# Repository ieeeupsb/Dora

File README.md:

View this project on [CADLAB.io](https://cadlab.io/project/1889). 

# Rasbot

## What is it?
This is a small differential terrestrial robot with all the sensors one can fit.
Its purpose is to have all the sensors and interfaces one can imagine so it can be used for research in various topics as well as different competitions.

Since its goal is to be resourceful in terms of sensing and actuating capabilities the design has expandability in mind. Therefore, there are a lot of exposed pins for modular expansions to the robot.

### Getting Support
There is extensive documentation on the Wiki page here on GitHub that covers the robot's design (hardware and software) as well as how to use this robot.

If you are a user of this robot and something is not working on your side please help us improve it. Open an issue here on GitHub!

### Contributing
Be it hardware or software, you can freely contribute to this project. Usually the Issues page here on GitHub has work that needs to be done. You are free to solve one yourself. Even if you are not familiar with hardware or software you can simply create new issues suggesting new things or changes/fixes to the current design.

This project is configured with CADLAB.io so visual differences of changes can be analysed.

If you are a contributor to this project keep in mind that pushing to the master branch is protected and can be only done by first creating a branch and then file a Pull Request which has to have at least two reviewers before it can be merged. This is meant to improve the quality of the project.

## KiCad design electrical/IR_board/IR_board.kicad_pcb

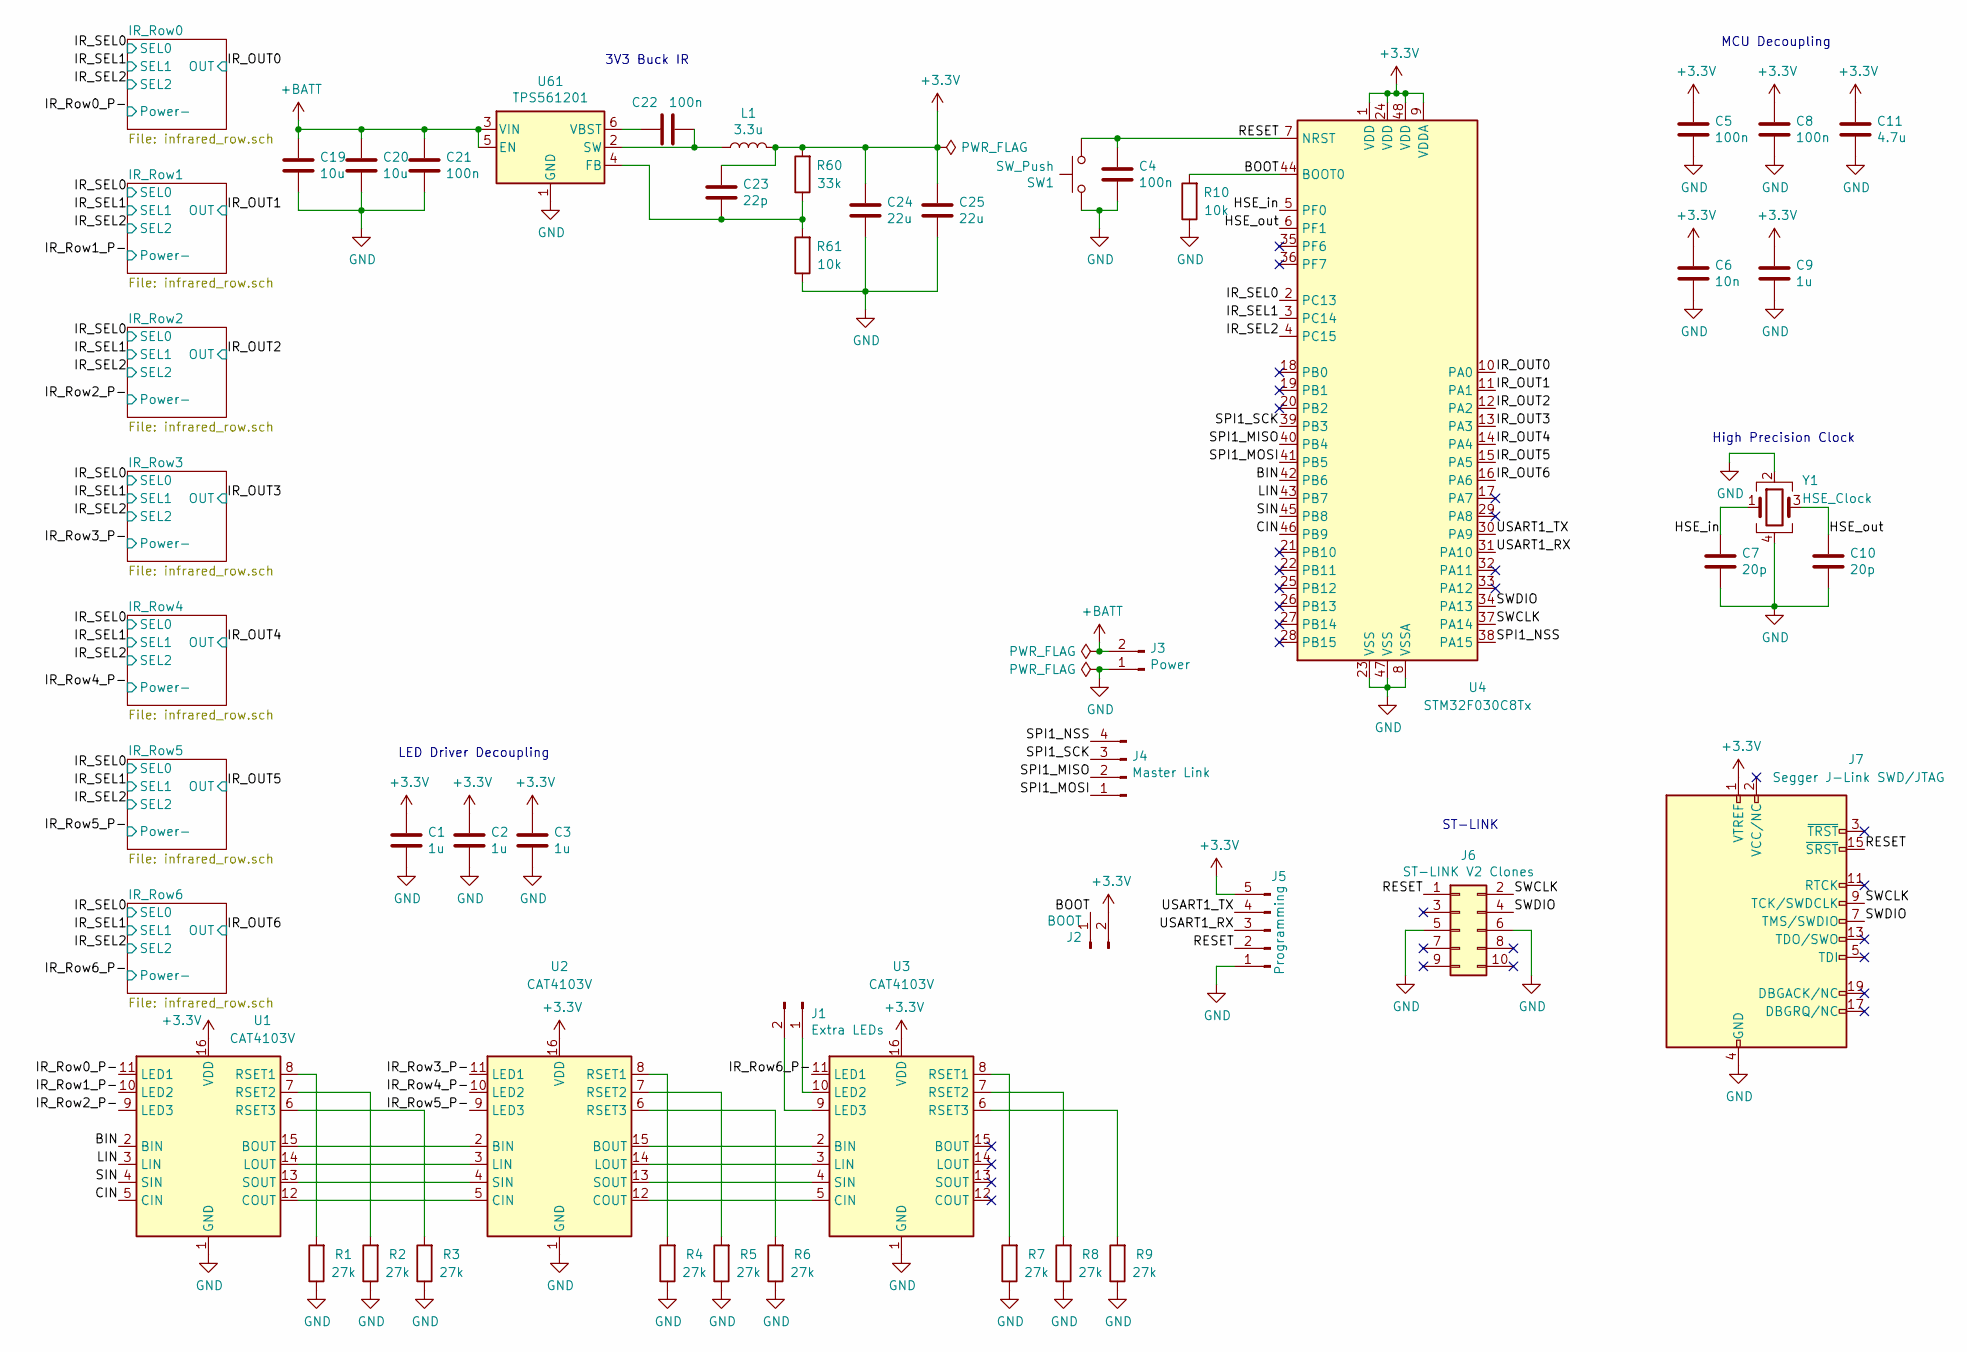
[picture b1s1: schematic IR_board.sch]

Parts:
C1, C2, C3, C9: 1u; C_0603_1608Metric
C4, C5, C8: 100n; C_0603_1608Metric
C6: 10n; C_0603_1608Metric
C7, C10: 20p; C_0603_1608Metric
C11: 4.7u; C_0603_1608Metric
C19, C20: 10u; C_1206_3216Metric
C21, C22: 100n; C_1206_3216Metric
C23: 22p; C_0603_1608Metric
C24, C25: 22u; C_0603_1608Metric
J1: Extra LEDs; PinHeader_1x02_P2.54mm_Horizontal
J2: BOOT; PinHeader_1x02_P2.54mm_Horizontal
J3: Power; JST_XH_S2B-XH-A-1_1x02_P2.50mm_Horizontal
J4: Master Link; JST_XH_S4B-XH-A-1_1x04_P2.50mm_Horizontal
J5: Programming; PinHeader_1x05_P2.54mm_Horizontal
J6: ST-LINK V2 Clones; IDC-Header_2x05_P2.54mm_Vertical
J7: Segger J-Link SWD/JTAG; IDC-Header_2x10_P2.54mm_Vertical
L1: 3.3u; L_Coilcraft_LPS4018
R1, R2, R3, R4, R5, R6, R7, R8, R9: 27k; R_0603_1608Metric
R10, R61: 10k; R_0603_1608Metric
R60: 33k; R_0603_1608Metric
SW1: SW_Push; SW_PUSH_6mm
U1, U2, U3: CAT4103V; SOIC-16_3.9x9.9mm_P1.27mm
U4: STM32F030C8Tx; LQFP-48_7x7mm_P0.5mm
U61: TPS561201; SOT-23-8
Y1: HSE_Clock; Crystal_SMD_5032-4Pin_5.0x3.2mm

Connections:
+3V3: C1.1, C2.1, C3.1, C5.1, C6.1, C8.1, C9.1, C11.1, C23.1, C24.1, C25.1, J2.2, J5.5, J7.1 (VTREF), L1.2, R60.2, U1.16 (VDD), U2.16 (VDD), U3.16 (VDD), U4.1 (VDD), U4.9 (VDDA), U4.24 (VDD), U4.48 (VDD); also elsewhere on the board
+BATT: C19.1, C20.1, C21.1, J3.2, U61.3 (VIN), U61.5 (EN); also elsewhere on the board
/BIN: U1.2 (BIN), U4.42 (PB6)
/BOOT: J2.1, R10.2, U4.44 (BOOT0)
/CIN: U1.5 (CIN), U4.46 (PB9)
/HSE_in: C7.1, U4.5 (PF0), Y1.1
/HSE_out: C10.1, U4.6 (PF1), Y1.3
/IR_OUT0: U4.10 (PA0); also elsewhere on the board
/IR_OUT1: U4.11 (PA1); also elsewhere on the board
/IR_OUT2: U4.12 (PA2); also elsewhere on the board
/IR_OUT3: U4.13 (PA3); also elsewhere on the board
/IR_OUT4: U4.14 (PA4); also elsewhere on the board
/IR_OUT5: U4.15 (PA5); also elsewhere on the board
/IR_OUT6: U4.16 (PA6); also elsewhere on the board
/IR_Row0_P-: U1.11 (LED1); also elsewhere on the board
/IR_Row1_P-: U1.10 (LED2); also elsewhere on the board
/IR_Row2_P-: U1.9 (LED3); also elsewhere on the board
/IR_Row3_P-: U2.11 (LED1); also elsewhere on the board
/IR_Row4_P-: U2.10 (LED2); also elsewhere on the board
/IR_Row5_P-: U2.9 (LED3); also elsewhere on the board
/IR_Row6_P-: U3.11 (LED1); also elsewhere on the board
/IR_SEL0: U4.2 (PC13); also elsewhere on the board
/IR_SEL1: U4.3 (PC14); also elsewhere on the board
/IR_SEL2: U4.4 (PC15); also elsewhere on the board
/LIN: U1.3 (LIN), U4.43 (PB7)
/RESET: C4.1, J5.2, J6.1, J7.15 (~SRST~), SW1.2, U4.7 (NRST)
/SIN: U1.4 (SIN), U4.45 (PB8)
/SPI1_MISO: J4.2, U4.40 (PB4)
/SPI1_MOSI: J4.1, U4.41 (PB5)
/SPI1_NSS: J4.4, U4.38 (PA15)
/SPI1_SCK: J4.3, U4.39 (PB3)
/SWCLK: J6.2, J7.9 (TCK/SWDCLK), U4.37 (PA14)
/SWDIO: J6.4, J7.7 (TMS/SWDIO), U4.34 (PA13)
/USART1_RX: J5.3, U4.31 (PA10)
/USART1_TX: J5.4, U4.30 (PA9)
GND: C1.2, C2.2, C3.2, C4.2, C5.2, C6.2, C7.2, C8.2, C9.2, C10.2, C11.2, C19.2, C20.2, C21.2, C24.2, C25.2, J3.1, J5.1, J6.5, J6.6, J7.4 (GND), J7.6 (GND), J7.8 (GND), J7.10 (GND), J7.12 (GND), J7.14 (GND), J7.16 (GND), J7.18 (GND), J7.20 (GND), R1.1, R2.1, R3.1, R4.1, R5.1, R6.1, R7.1, R8.1, R9.1, R10.1, R61.1, SW1.1, U1.1 (GND), U2.1 (GND), U3.1 (GND), U4.8 (VSSA), U4.23 (VSS), U4.47 (VSS), U61.1 (GND), Y1.2, Y1.4; also elsewhere on the board
unnamed: C22.1, U61.6 (VBST)
unnamed: C22.2, L1.1, U61.2 (SW)
unnamed: C23.2, R60.1, R61.2, U61.4 (FB)
unnamed: J1.1, U3.10 (LED2)
unnamed: J1.2, U3.9 (LED3)
unnamed: R1.2, U1.8 (RSET1)
unnamed: R2.2, U1.7 (RSET2)
unnamed: R3.2, U1.6 (RSET3)
unnamed: R4.2, U2.8 (RSET1)
unnamed: R5.2, U2.7 (RSET2)
unnamed: R6.2, U2.6 (RSET3)
unnamed: R7.2, U3.8 (RSET1)
unnamed: R8.2, U3.7 (RSET2)
unnamed: R9.2, U3.6 (RSET3)
unnamed: U1.12 (COUT), U2.5 (CIN)
unnamed: U1.13 (SOUT), U2.4 (SIN)
unnamed: U1.14 (LOUT), U2.3 (LIN)
unnamed: U1.15 (BOUT), U2.2 (BIN)
unnamed: U2.12 (COUT), U3.5 (CIN)
unnamed: U2.13 (SOUT), U3.4 (SIN)
unnamed: U2.14 (LOUT), U3.3 (LIN)
unnamed: U2.15 (BOUT), U3.2 (BIN)

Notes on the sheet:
LED Driver Decoupling
ST-LINK
High Precision Clock
MCU Decoupling
3V3 Buck IR

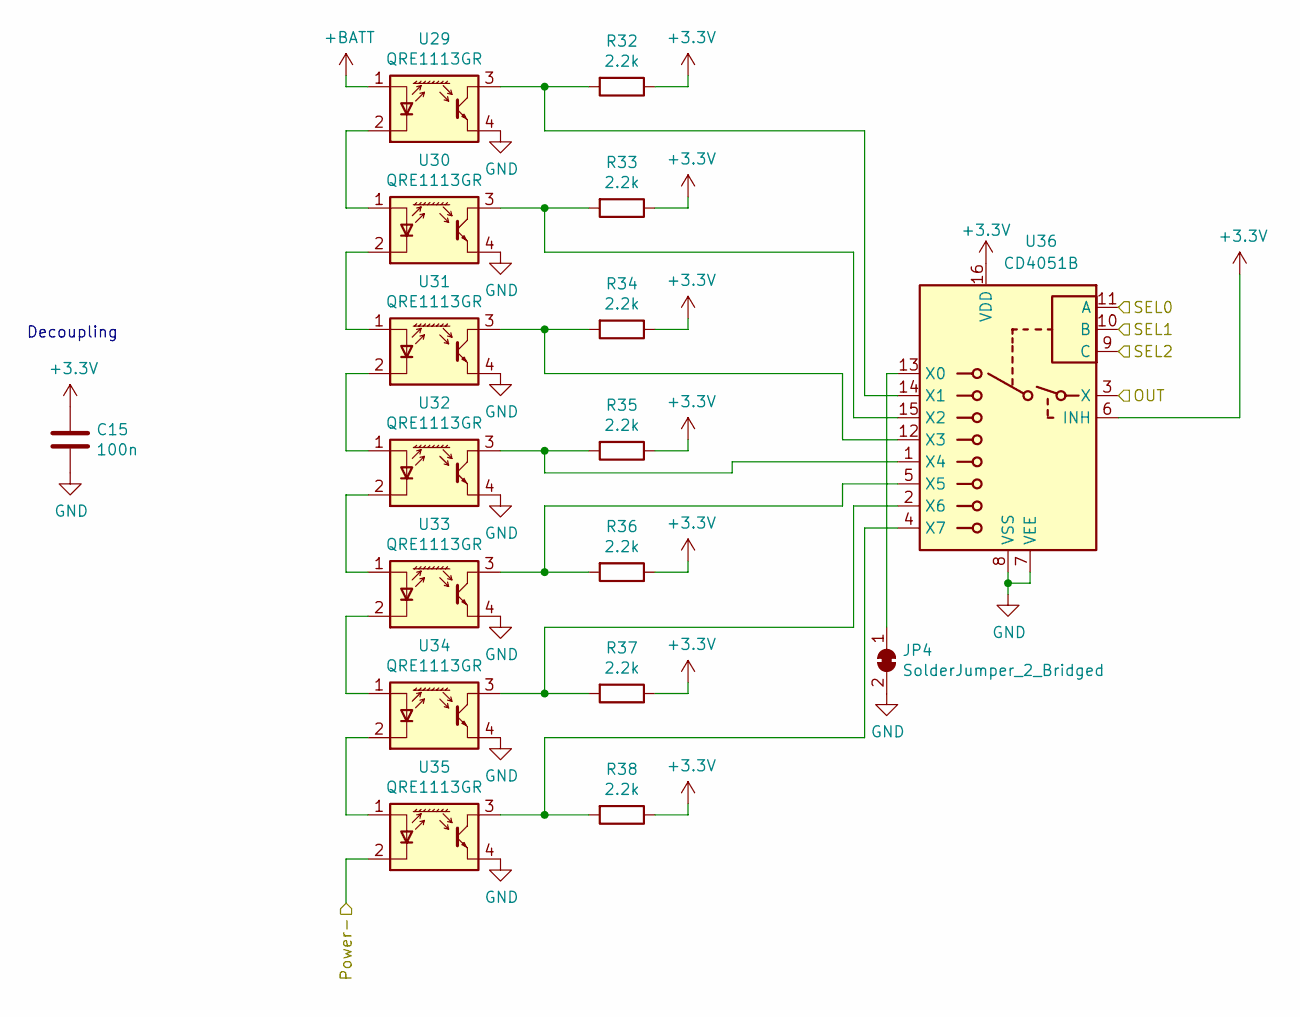
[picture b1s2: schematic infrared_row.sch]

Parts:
C17: 100n; C_0603_1608Metric
JP4: SolderJumper_2_Bridged; SolderJumper-2_P1.3mm_Bridged_Pad1.0x1.5mm
R46, R47, R48, R49, R50, R51, R52: 2.2k; R_0603_1608Metric
U45, U46, U47, U48, U49, U50, U51: QRE1113GR; OnSemi_CASE100CY
U52: CD4051B; SOP-16_4.55x10.3mm_P1.27mm

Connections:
+3V3: C17.1, R46.1, R47.1, R48.1, R49.1, R50.1, R51.1, R52.1, U52.6 (INH), U52.16 (VDD); also elsewhere on the board
+BATT: U45.1 (A); also elsewhere on the board
/IR_OUT6: U52.3 (X); also elsewhere on the board
/IR_Row6_P-: U51.2 (K); also elsewhere on the board
/IR_SEL0: U52.11 (A); also elsewhere on the board
/IR_SEL1: U52.10 (B); also elsewhere on the board
/IR_SEL2: U52.9 (C); also elsewhere on the board
GND: C17.2, JP4.2 (B), U45.4, U46.4, U47.4, U48.4, U49.4, U50.4, U51.4, U52.7 (VEE), U52.8 (VSS); also elsewhere on the board
unnamed: R46.2, U45.3, U52.14 (X1)
unnamed: R47.2, U46.3, U52.15 (X2)
unnamed: R48.2, U47.3, U52.12 (X3)
unnamed: R49.2, U48.3, U52.1 (X4)
unnamed: R50.2, U49.3, U52.5 (X5)
unnamed: R51.2, U50.3, U52.2 (X6)
unnamed: R52.2, U51.3, U52.4 (X7)
unnamed: U45.2 (K), U46.1 (A)
unnamed: U46.2 (K), U47.1 (A)
unnamed: U47.2 (K), U48.1 (A)
unnamed: U48.2 (K), U49.1 (A)
unnamed: U49.2 (K), U50.1 (A)
unnamed: U50.2 (K), U51.1 (A)

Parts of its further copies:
C12, C13, C14, C15, C16, C18: 100n; C_0603_1608Metric
JP1, JP2, JP3, JP5, JP6, JP7: SolderJumper_2_Bridged; SolderJumper-2_P1.3mm_Bridged_Pad1.0x1.5mm
R11, R12, R13, R14, R15, R16, R17, R18, R19, R20, R21, R22, R23, R24, R25, R26, R27, R28, R29, R30, R31, R32, R33, R34, R35, R36, R37, R38, R39, R40, R41, R42, R43, R44, R45, R53, R54, R55, R56, R57, R58, R59: 2.2k; R_0603_1608Metric
U5, U6, U7, U8, U9, U10, U11, U13, U14, U15, U16, U17, U18, U19, U21, U22, U23, U24, U25, U26, U27, U29, U30, U31, U32, U33, U34, U35, U37, U38, U39, U40, U41, U42, U43, U53, U54, U55, U56, U57, U58, U59: QRE1113GR; OnSemi_CASE100CY
U12, U20, U28, U36, U44, U60: CD4051B; SOP-16_4.55x10.3mm_P1.27mm

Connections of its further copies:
+3V3: C12.1, C13.1, C14.1, C15.1, C16.1, C18.1, R11.1, R12.1, R13.1, R14.1, R15.1, R16.1, R17.1, R18.1, R19.1, R20.1, R21.1, R22.1, R23.1, R24.1, R25.1, R26.1, R27.1, R28.1, R29.1, R30.1, R31.1, R32.1, R33.1, R34.1, R35.1, R36.1, R37.1, R38.1, R39.1, R40.1, R41.1, R42.1, R43.1, R44.1, R45.1, R53.1, R54.1, R55.1, R56.1, R57.1, R58.1, R59.1, U12.6 (INH), U12.16 (VDD), U20.6 (INH), U20.16 (VDD), U28.6 (INH), U28.16 (VDD), U36.6 (INH), U36.16 (VDD), U44.6 (INH), U44.16 (VDD), U60.6 (INH), U60.16 (VDD); also elsewhere on the board
+BATT: U5.1 (A), U13.1 (A), U21.1 (A), U29.1 (A), U37.1 (A), U53.1 (A); also elsewhere on the board
/IR_OUT0: U60.3 (X); also elsewhere on the board
/IR_OUT1: U12.3 (X); also elsewhere on the board
/IR_OUT2: U44.3 (X); also elsewhere on the board
/IR_OUT3: U20.3 (X); also elsewhere on the board
/IR_OUT4: U28.3 (X); also elsewhere on the board
/IR_OUT5: U36.3 (X); also elsewhere on the board
/IR_Row0_P-: U59.2 (K); also elsewhere on the board
/IR_Row1_P-: U11.2 (K); also elsewhere on the board
/IR_Row2_P-: U43.2 (K); also elsewhere on the board
/IR_Row3_P-: U19.2 (K); also elsewhere on the board
/IR_Row4_P-: U27.2 (K); also elsewhere on the board
/IR_Row5_P-: U35.2 (K); also elsewhere on the board
/IR_SEL0: U12.11 (A), U20.11 (A), U28.11 (A), U36.11 (A), U44.11 (A), U60.11 (A); also elsewhere on the board
/IR_SEL1: U12.10 (B), U20.10 (B), U28.10 (B), U36.10 (B), U44.10 (B), U60.10 (B); also elsewhere on the board
/IR_SEL2: U12.9 (C), U20.9 (C), U28.9 (C), U36.9 (C), U44.9 (C), U60.9 (C); also elsewhere on the board
GND: C12.2, C13.2, C14.2, C15.2, C16.2, C18.2, JP1.2 (B), JP2.2 (B), JP3.2 (B), JP5.2 (B), JP6.2 (B), JP7.2 (B), U5.4, U6.4, U7.4, U8.4, U9.4, U10.4, U11.4, U12.7 (VEE), U12.8 (VSS), U13.4, U14.4, U15.4, U16.4, U17.4, U18.4, U19.4, U20.7 (VEE), U20.8 (VSS), U21.4, U22.4, U23.4, U24.4, U25.4, U26.4, U27.4, U28.7 (VEE), U28.8 (VSS), U29.4, U30.4, U31.4, U32.4, U33.4, U34.4, U35.4, U36.7 (VEE), U36.8 (VSS), U37.4, U38.4, U39.4, U40.4, U41.4, U42.4, U43.4, U44.7 (VEE), U44.8 (VSS), U53.4, U54.4, U55.4, U56.4, U57.4, U58.4, U59.4, U60.7 (VEE), U60.8 (VSS); also elsewhere on the board
unnamed: JP1.1 (A), U12.13 (X0)
unnamed: JP2.1 (A), U20.13 (X0)
unnamed: JP3.1 (A), U28.13 (X0)
unnamed: JP5.1 (A), U44.13 (X0)
unnamed: JP7.1 (A), U60.13 (X0)
unnamed: R11.2, U5.3, U12.14 (X1)
unnamed: R12.2, U6.3, U12.15 (X2)
unnamed: R13.2, U7.3, U12.12 (X3)
unnamed: R14.2, U8.3, U12.1 (X4)
unnamed: R15.2, U9.3, U12.5 (X5)
unnamed: R16.2, U10.3, U12.2 (X6)
unnamed: R17.2, U11.3, U12.4 (X7)
unnamed: R18.2, U13.3, U20.14 (X1)
unnamed: R19.2, U14.3, U20.15 (X2)
unnamed: R20.2, U15.3, U20.12 (X3)
unnamed: R21.2, U16.3, U20.1 (X4)
unnamed: R22.2, U17.3, U20.5 (X5)
unnamed: R23.2, U18.3, U20.2 (X6)
unnamed: R24.2, U19.3, U20.4 (X7)
unnamed: R25.2, U21.3, U28.14 (X1)
unnamed: R26.2, U22.3, U28.15 (X2)
unnamed: R27.2, U23.3, U28.12 (X3)
unnamed: R28.2, U24.3, U28.1 (X4)
unnamed: R29.2, U25.3, U28.5 (X5)
unnamed: R30.2, U26.3, U28.2 (X6)
unnamed: R31.2, U27.3, U28.4 (X7)
unnamed: R32.2, U29.3, U36.14 (X1)
unnamed: R33.2, U30.3, U36.15 (X2)
unnamed: R34.2, U31.3, U36.12 (X3)
unnamed: R35.2, U32.3, U36.1 (X4)
unnamed: R36.2, U33.3, U36.5 (X5)
unnamed: R37.2, U34.3, U36.2 (X6)
unnamed: R38.2, U35.3, U36.4 (X7)
unnamed: R39.2, U37.3, U44.14 (X1)
unnamed: R40.2, U38.3, U44.15 (X2)
unnamed: R41.2, U39.3, U44.12 (X3)
unnamed: R42.2, U40.3, U44.1 (X4)
unnamed: R43.2, U41.3, U44.5 (X5)
unnamed: R44.2, U42.3, U44.2 (X6)
unnamed: R45.2, U43.3, U44.4 (X7)
unnamed: R53.2, U53.3, U60.14 (X1)
unnamed: R54.2, U54.3, U60.15 (X2)
unnamed: R55.2, U55.3, U60.12 (X3)
unnamed: R56.2, U56.3, U60.1 (X4)
unnamed: R57.2, U57.3, U60.5 (X5)
unnamed: R58.2, U58.3, U60.2 (X6)
unnamed: R59.2, U59.3, U60.4 (X7)
unnamed: U5.2 (K), U6.1 (A)
unnamed: U6.2 (K), U7.1 (A)
unnamed: U7.2 (K), U8.1 (A)
unnamed: U8.2 (K), U9.1 (A)
unnamed: U9.2 (K), U10.1 (A)
unnamed: U10.2 (K), U11.1 (A)
unnamed: U13.2 (K), U14.1 (A)
unnamed: U14.2 (K), U15.1 (A)
unnamed: U15.2 (K), U16.1 (A)
unnamed: U16.2 (K), U17.1 (A)
unnamed: U17.2 (K), U18.1 (A)
unnamed: U18.2 (K), U19.1 (A)
unnamed: U21.2 (K), U22.1 (A)
unnamed: U22.2 (K), U23.1 (A)
unnamed: U23.2 (K), U24.1 (A)
unnamed: U24.2 (K), U25.1 (A)
unnamed: U25.2 (K), U26.1 (A)
unnamed: U26.2 (K), U27.1 (A)
unnamed: U29.2 (K), U30.1 (A)
unnamed: U30.2 (K), U31.1 (A)
unnamed: U31.2 (K), U32.1 (A)
unnamed: U32.2 (K), U33.1 (A)
unnamed: U33.2 (K), U34.1 (A)
unnamed: U34.2 (K), U35.1 (A)
unnamed: U37.2 (K), U38.1 (A)
unnamed: U38.2 (K), U39.1 (A)
unnamed: U39.2 (K), U40.1 (A)
unnamed: U40.2 (K), U41.1 (A)
unnamed: U41.2 (K), U42.1 (A)
unnamed: U42.2 (K), U43.1 (A)
unnamed: U53.2 (K), U54.1 (A)
unnamed: U54.2 (K), U55.1 (A)
unnamed: U55.2 (K), U56.1 (A)
unnamed: U56.2 (K), U57.1 (A)
unnamed: U57.2 (K), U58.1 (A)
unnamed: U58.2 (K), U59.1 (A)

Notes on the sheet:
Decoupling

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
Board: 2 copper layers, 164 parts (0 on the bottom side), 156 nets, no tracks yet.

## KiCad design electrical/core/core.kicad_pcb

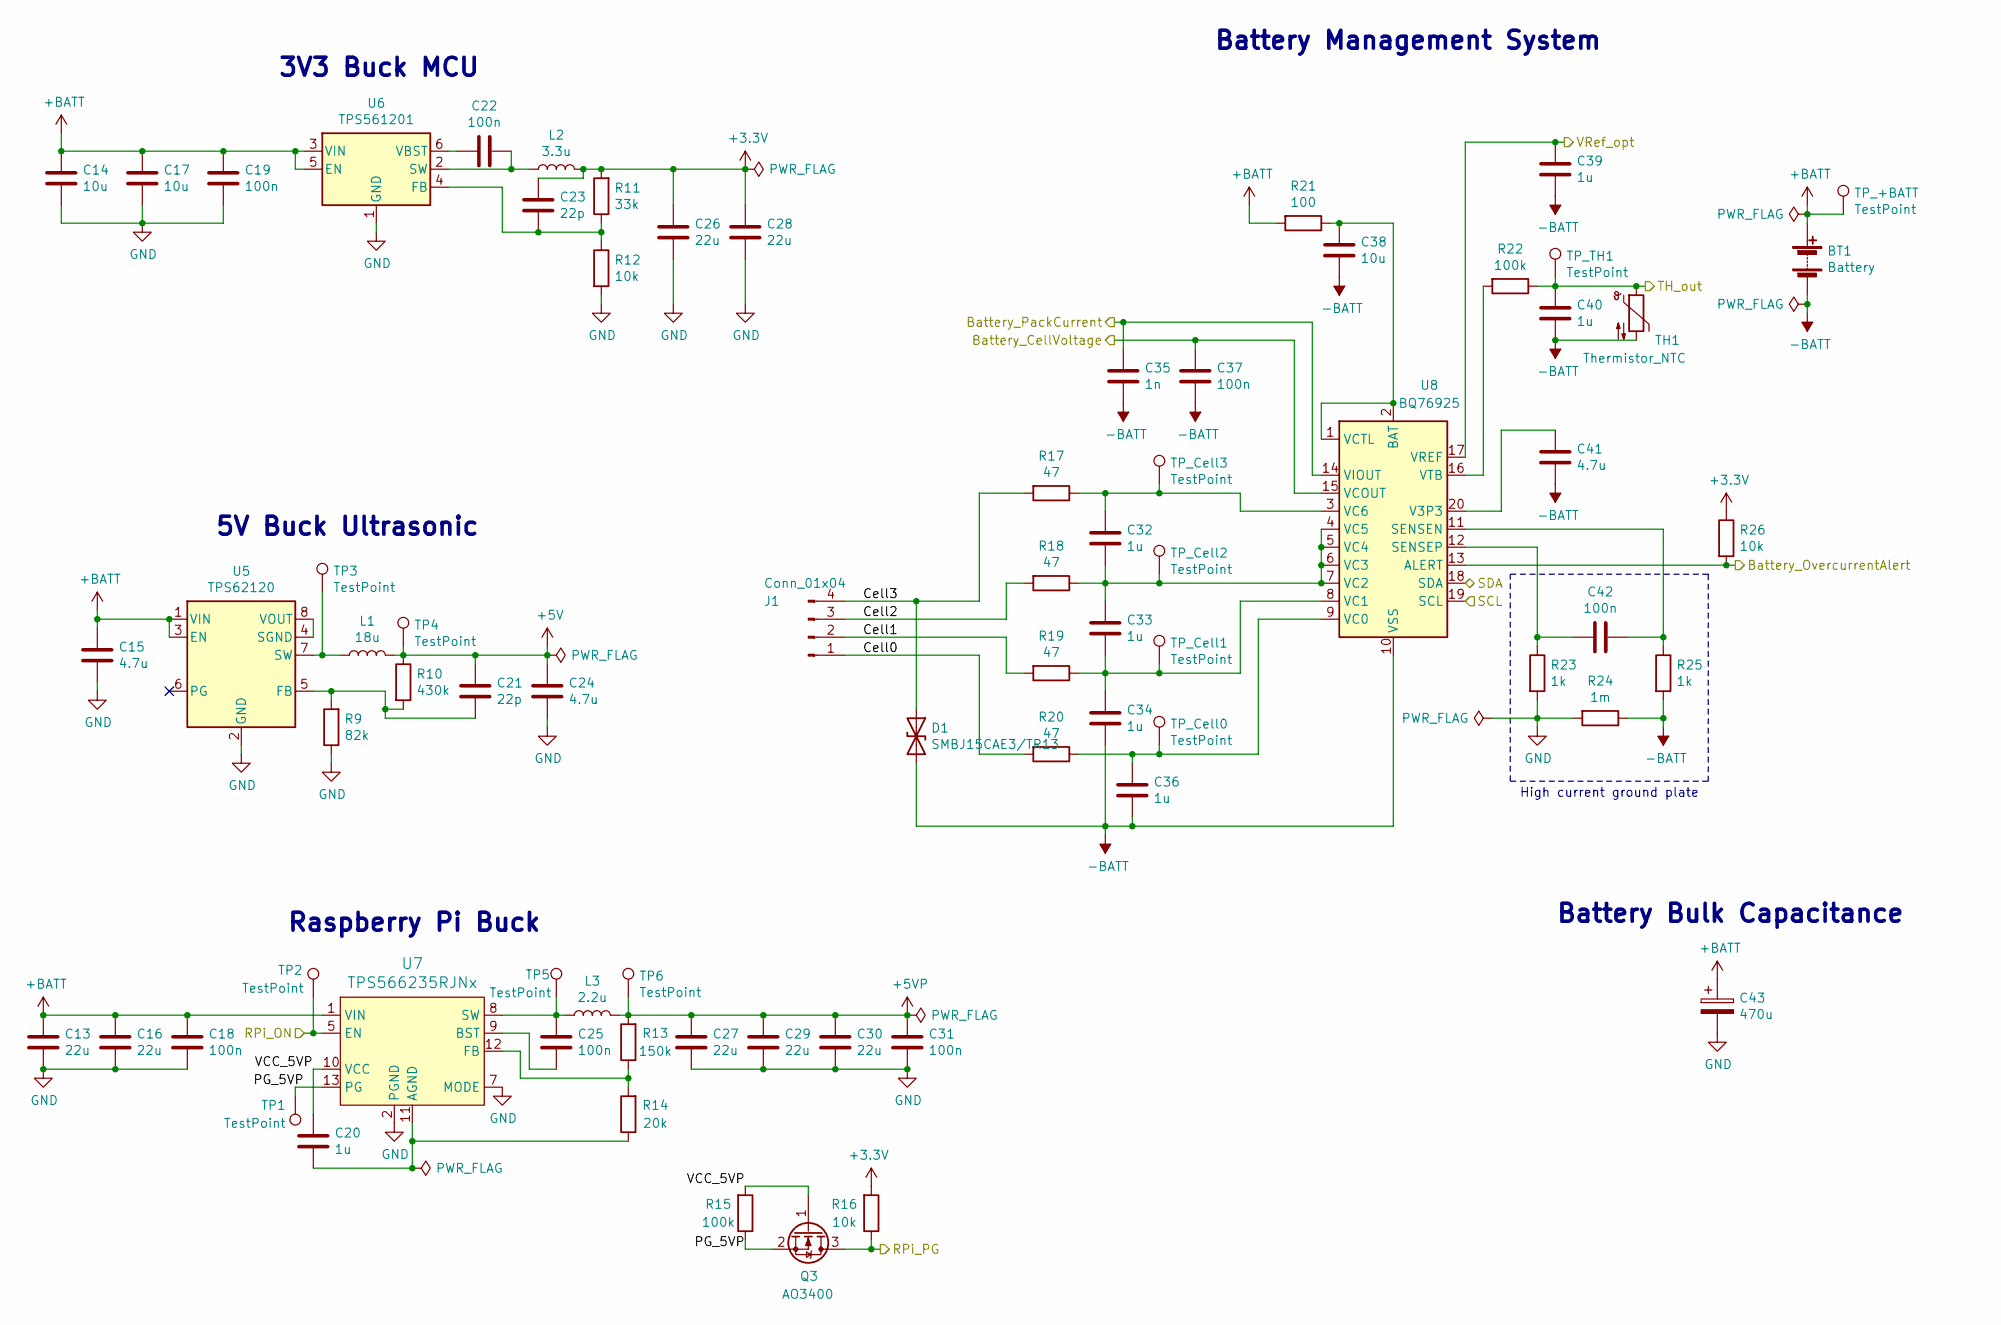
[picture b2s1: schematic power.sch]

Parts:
BT1: Battery; SolderWire-2.5sqmm_1x02_P7.2mm_D2.4mm_OD3.6mm_Relief_12AWG_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
C13, C16: 22u; C_1206_3216Metric
C14, C17, C38: 10u; C_1206_3216Metric
C15: 4.7u; C_1206_3216Metric
C18, C19, C22, C25, C42: 100n; C_1206_3216Metric
C20, C32, C33, C34, C36, C39, C40: 1u; C_0603_1608Metric
C21, C23: 22p; C_0603_1608Metric
C24, C41: 4.7u; C_0603_1608Metric
C26, C27, C28, C29, C30: 22u; C_0603_1608Metric
C31, C37: 100n; C_0603_1608Metric
C35: 1n; C_0603_1608Metric
C43: 470u; CP_Elec_10x10
D1: SMBJ15CAE3/TR13; D_SMB
J1: Conn_01x04; JST_XH_S4B-XH-A-1_1x04_P2.50mm_Horizontal
L1: 18u; L_Coilcraft_LPS4018
L2: 3.3u; L_Coilcraft_LPS4018
L3: 2.2u; L_10.4x10.4_H4.8
Q3: AO3400; SOT-23
R9: 82k; R_0603_1608Metric
R10: 430k; R_0603_1608Metric
R11: 33k; R_0603_1608Metric
R12, R16, R26: 10k; R_0603_1608Metric
R13: 150k; R_0603_1608Metric
R14: 20k; R_0603_1608Metric
R15, R22: 100k; R_0603_1608Metric
R17, R18, R19, R20: 47; R_0603_1608Metric
R21: 100; R_0603_1608Metric
R23, R25: 1k; R_0603_1608Metric
R24: 1m; R_2512_6332Metric
TH1: Thermistor_NTC; PinHeader_1x02_P2.54mm_Horizontal
TP1, TP2, TP3, TP4, TP5, TP6: TestPoint; TestPoint_Pad_D1.0mm
TP_+BATT: TestPoint; TestPoint_Pad_D1.0mm
TP_Cell0, TP_Cell1, TP_Cell2, TP_Cell3: TestPoint; TestPoint_Pad_D1.0mm
TP_TH1: TestPoint; TestPoint_Pad_D1.0mm
U5: TPS62120; SOT-23-8
U6: TPS561201; SOT-23-8
U7: TPS566235RJNx; VQFN-13-1EP_3x3mm_P0.5mm_EP1.6x1.6mm
U8: BQ76925; TSSOP-20_4.4x6.5mm_P0.65mm

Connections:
+3V3: C23.1, C26.1, C28.1, L2.2, R11.2, R16.2, R26.1; also elsewhere on the board
+5V: C21.1, C24.1, L1.2, R10.1, TP4.1; also elsewhere on the board
+5VP: C27.1, C29.1, C30.1, C31.1, L3.2, R13.2, TP6.1; also elsewhere on the board
+BATT: BT1.1 (+), C13.1, C14.1, C15.1, C16.1, C17.1, C18.1, C19.1, C43.1, R21.2, TP_+BATT.1, U5.1 (VIN), U5.3 (EN), U6.3 (VIN), U6.5 (EN), U7.1 (VIN); also elsewhere on the board
-BATT: BT1.2 (-), C34.2, C35.2, C36.2, C37.2, C38.2, C39.2, C40.2, C41.2, D1.2 (A2), R24.1, R25.2, TH1.2, U8.10 (VSS)
/Battery_Cell_Voltage: C37.1, U8.15 (VCOUT); also elsewhere on the board
/Battery_Current: C35.1, U8.14 (VIOUT); also elsewhere on the board
/Battery_Overcurrent: R26.2, U8.13 (ALERT); also elsewhere on the board
/Battery_Temperature: C40.1, R22.1, TH1.1, TP_TH1.1; also elsewhere on the board
/I2C1_SCL: U8.19 (SCL); also elsewhere on the board
/I2C1_SDA: U8.18 (SDA); also elsewhere on the board
/Power/Cell0: J1.1, R20.2
/Power/Cell1: J1.2, R19.2
/Power/Cell2: J1.3, R18.2
/Power/Cell3: D1.1 (A1), J1.4, R17.2
/Power/PG_5VP: Q3.2 (S), R15.1, TP1.1, U7.13 (PG)
/Power/VCC_5VP: C20.1, Q3.1 (G), R15.2, U7.10 (VCC)
/RPi_EN: TP2.1, U7.5 (EN); also elsewhere on the board
/RPi_PG: Q3.3 (D), R16.1; also elsewhere on the board
/Vref_opt: C39.1, U8.17 (VREF); also elsewhere on the board
GND: C13.2, C14.2, C15.2, C16.2, C17.2, C18.2, C19.2, C24.2, C26.2, C27.2, C28.2, C29.2, C30.2, C31.2, C43.2, R9.1, R12.2, R23.2, R24.2, U5.2 (GND), U6.1 (GND), U7.2 (PGND), U7.3 (PGND), U7.4 (PGND), U7.6 (PGND), U7.7 (MODE); also elsewhere on the board
unnamed: C20.2, R14.1, U7.11 (AGND)
unnamed: C21.2, R9.2, R10.2, U5.5 (FB)
unnamed: C22.1, U6.6 (VBST)
unnamed: C22.2, L2.1, U6.2 (SW)
unnamed: C23.2, R11.1, R12.1, U6.4 (FB)
unnamed: C25.1, L3.1, TP5.1, U7.8 (SW)
unnamed: C25.2, U7.9 (BST)
unnamed: C32.1, R17.1, TP_Cell3.1, U8.3 (VC6)
unnamed: C32.2, C33.1, R18.1, TP_Cell2.1, U8.4 (VC5), U8.5 (VC4), U8.6 (VC3), U8.7 (VC2)
unnamed: C33.2, C34.1, R19.1, TP_Cell1.1, U8.8 (VC1)
unnamed: C36.1, R20.1, TP_Cell0.1, U8.9 (VC0)
unnamed: C38.1, R21.1, U8.1 (VCTL), U8.2 (BAT)
unnamed: C41.1, U8.20 (V3P3)
unnamed: C42.1, R23.1, U8.12 (SENSEP)
unnamed: C42.2, R25.1, U8.11 (SENSEN)
unnamed: L1.1, TP3.1, U5.7 (SW)
unnamed: R13.1, R14.2, U7.12 (FB)
unnamed: R22.2, U8.16 (VTB)
unnamed: U5.4 (SGND), U5.8 (VOUT)

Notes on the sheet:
Battery Management System
High current ground plate
Raspberry Pi Buck
5V Buck Ultrasonic
3V3 Buck MCU
Battery Bulk Capacitance

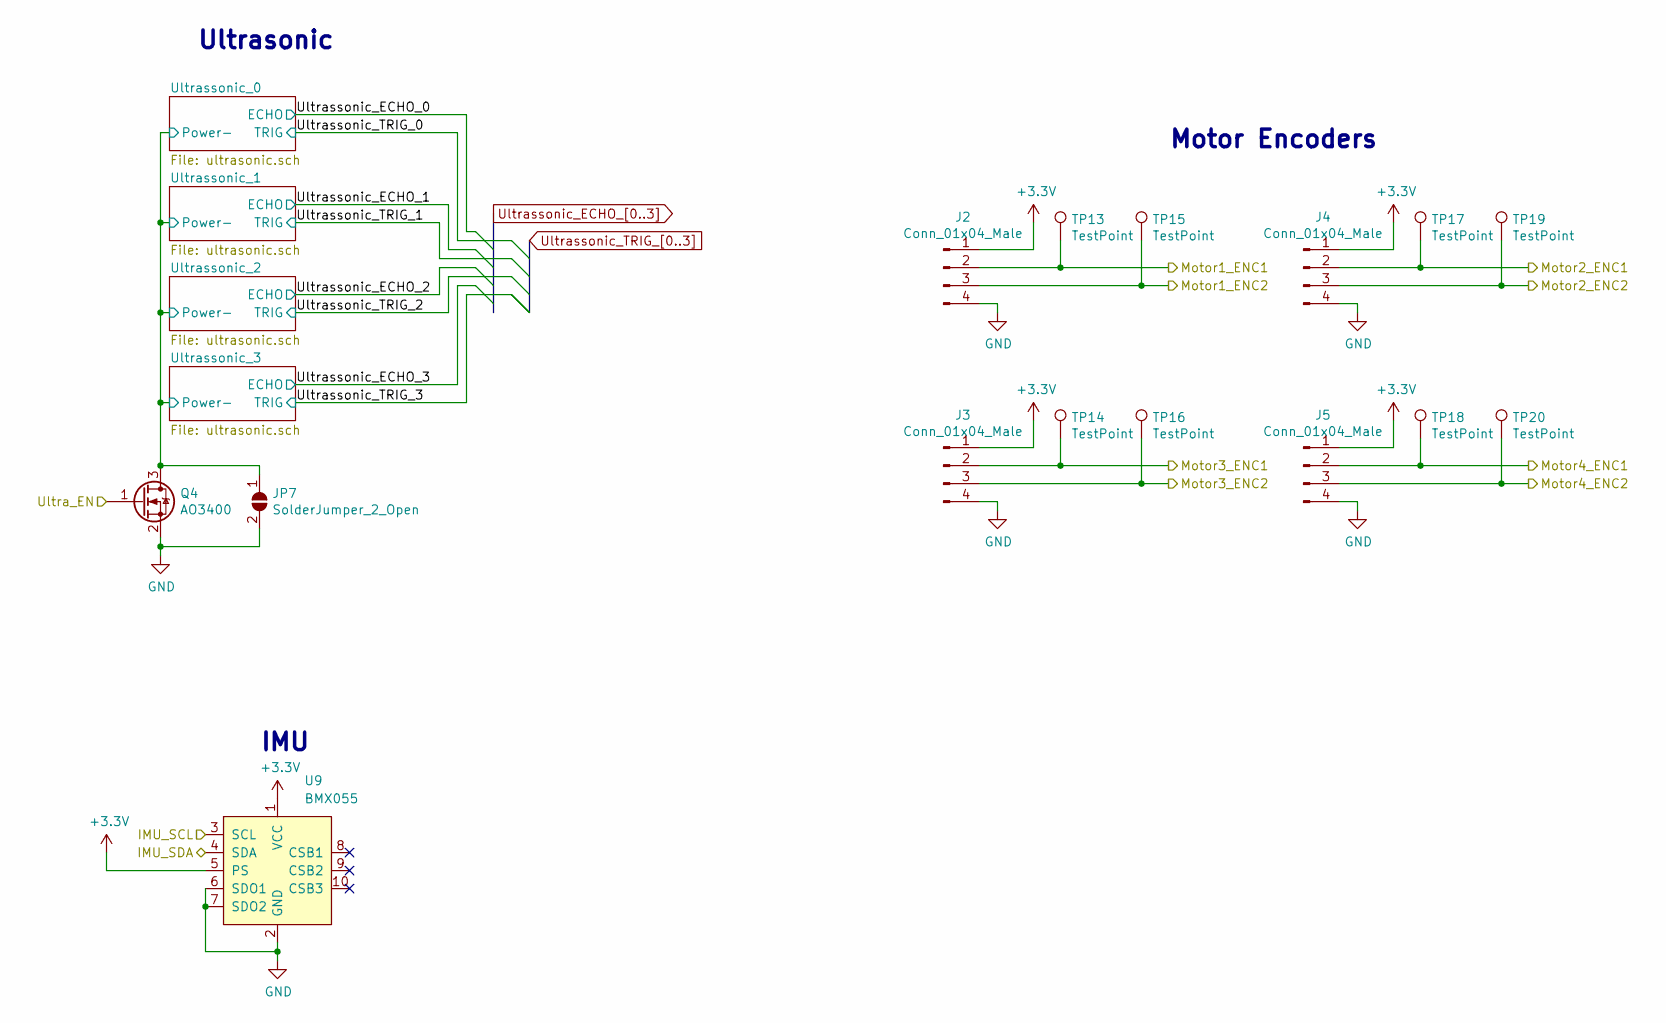
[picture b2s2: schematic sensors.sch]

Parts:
J2, J3, J4, J5: Conn_01x04_Male; JST_XH_S4B-XH-A-1_1x04_P2.50mm_Horizontal
JP7: SolderJumper_2_Open; SolderJumper-2_P1.3mm_Open_Pad1.0x1.5mm
Q4: AO3400; SOT-23
TP13, TP14, TP15, TP16, TP17, TP18, TP19, TP20: TestPoint; TestPoint_Pad_D1.0mm
U9: BMX055; PinSocket_1x10_P2.54mm_Vertical

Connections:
+3V3: J2.1, J3.1, J4.1, J5.1, U9.1 (VCC), U9.5 (PS); also elsewhere on the board
/I2C2_SCL: U9.3 (SCL); also elsewhere on the board
/I2C2_SDA: U9.4 (SDA); also elsewhere on the board
/Motor1_ENC1: J2.2, TP13.1; also elsewhere on the board
/Motor1_ENC2: J2.3, TP15.1; also elsewhere on the board
/Motor2_ENC1: J4.2, TP17.1; also elsewhere on the board
/Motor2_ENC2: J4.3, TP19.1; also elsewhere on the board
/Motor3_ENC1: J3.2, TP14.1; also elsewhere on the board
/Motor3_ENC2: J3.3, TP16.1; also elsewhere on the board
/Motor4_ENC1: J5.2, TP18.1; also elsewhere on the board
/Motor4_ENC2: J5.3, TP20.1; also elsewhere on the board
/Sensors/Ultrassonic_0/Power-: JP7.1 (A), Q4.3 (D); also elsewhere on the board
/Ultra_EN: Q4.1 (G); also elsewhere on the board
GND: J2.4, J3.4, J4.4, J5.4, JP7.2 (B), Q4.2 (S), U9.2 (GND), U9.6 (SDO1), U9.7 (SDO2); also elsewhere on the board

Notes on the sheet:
Motor Encoders
Ultrasonic
IMU
